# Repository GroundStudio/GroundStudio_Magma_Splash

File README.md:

GroundStudio Magma Splash
====================================

Get it from [ardushop.ro](https://ardushop.ro/ro/home/2496-placa-de-dezvoltare-magma-splash.html)

Explore all the GroundStudio products at [GroundStudio.ro](https://groundstudio.ro/)

Description
-------------------
STM32F411CEU6 based development board wih high-performance ARM® Cortex®-M4 32-bit RISC core operating at a frequency of up to 100 MHz, 512kBytes of Flash memory, 128kBytes SRAM, 24 PWM, 5 SPI, 3 UART, 32 Digital Pins and 10 channel 12 bit ADC Pins.

Contents
-------------------

* [/Documentation](https://github.com/GroundStudio/GroundStudio_Magma_Splash/tree/main/Documentation) -- Pinout.
* [/Hardware](https://github.com/GroundStudio/GroundStudio_Magma_Splash/tree/main/Hardware) -- Schematics, layout.

Versions
-------------------
*(Not all tags shown)*

* [REV0.01]

License
-------------------

This is released under the [Attribution-ShareAlike 4.0 International (CC BY-SA 4.0)](https://creativecommons.org/licenses/by-sa/4.0/) license.
**You are welcome to use this for commercial purposes.**

Please consider contributing back to this project or others to help the open-source hardware community continue to thrive and grow!

Certifications:

[Open Source Hardware Association](https://certification.oshwa.org/ro000009.html)   
   
[
](https://certification.oshwa.org/ro000009.html)

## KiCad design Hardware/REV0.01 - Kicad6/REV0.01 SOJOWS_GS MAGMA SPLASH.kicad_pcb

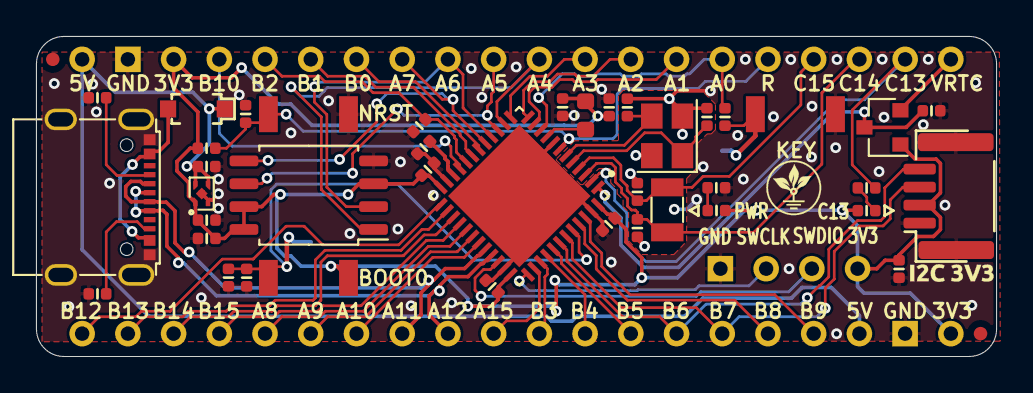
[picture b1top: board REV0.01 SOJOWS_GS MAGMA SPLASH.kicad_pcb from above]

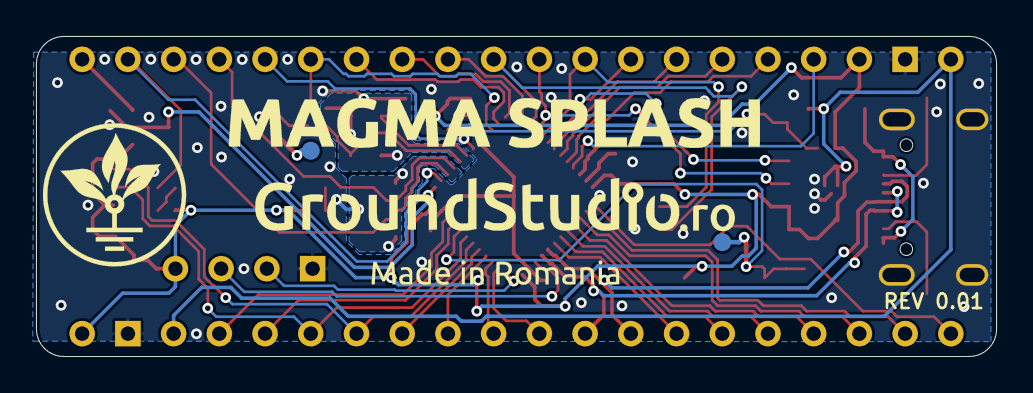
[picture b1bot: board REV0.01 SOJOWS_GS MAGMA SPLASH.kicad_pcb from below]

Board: 2 copper layers, 53.3 x 17.8 mm, 47 parts (2 on the bottom side), 51 nets.

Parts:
C1, C2, C3, C4, C5, C8, C9, C16, C17: 100nF; C_0402_1005Metric_Alternative
C6, C7, C10: 1uF; C_0402_1005Metric_Alternative
C11: 2.2uF; C_0402_1005Metric_Alternative
C12, C13, C14, C15: 12pF; C_0402_1005Metric_Alternative
D1: D_Schottky; SOD-123
D2: BAT54C; SOT-23
FID1, FID2: Fiducial; Fiducial_0.75mm_Mask1.5mm
J1, J2: Conn_01x20; PinHeader_1x20_P2.54mm_Vertical_Male
J3: Conn_01x04; PinHeader_1x04_P2.54mm_Vertical_Male
L1: L; L_0603_1608Metric
LED1: GREEN; LED_0402_1005Metric_Alternative
LED2: BLUE; LED_0402_1005Metric_Alternative
R1, R2, R4: 10k; R_0402_1005Metric_Alternative
R3: 330; R_0402_1005Metric_Alternative
R5, R6: 5.1k; R_0402_1005Metric_Alternative
R7, R8: 1k; R_0402_1005Metric_Alternative
RESET1: TS342A2P-WZ
SW1, SW2: TS342A2P-WZ
TP2: TestPoint
TPe: TestPoint
U1: ME6211C33U4AG-N; FBP1-1-4
U2: STM32F411CEU6; UFQFPN-48-1EP_7x7mm_P0.5mm_EP5.6x5.6mm
U3: W25Q32JVSSIQ; SOIC-8_5.275x5.275mm_P1.27mm
USB1: USB_C_FULL; USB_C_C167321
X1: i2c_3V3; SH__1x04_P1.00mm_Horizontal
Y1: SF32K32768D71T01; Crystal_SMD_3215-2Pin_3.2x1.5mm
Y2: S3225000121060; Crystal_SMD_3225-4Pin_3.2x2.5mm

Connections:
+3V3: C3.1, C4.1, C5.1, C7.1, C8.1, C9.1, C10.1, C16.1, D2.1, J1.3, J2.20, J3.4, L1.2, LED1.2, LED2.2, R1.1, SW2.2, U1.1, U2.24, U2.36, U2.48, U3.3, U3.7, U3.8, X1.2
+5V: C6.1, D1.1, J1.1, J2.18, U1.3, U1.4
A_D+: J2.9, U2.33, USB1.A6, USB1.B6
A_D-: J2.8, U2.32, USB1.A7, USB1.B7
BOOT0: C1.2, R2.1, SW2.1, TPe.~, U2.44
GND: C1.1, C2.2, C3.2, C4.2, C5.2, C6.2, C7.2, C8.2, C9.2, C10.2, C11.2, C12.2, C13.2, C14.2, C15.2, C16.2, C17.2, J1.2, J2.19, J3.1, R2.2, R4.2, R5.1, R6.2, R7.1, RESET1.1, SW1.2, U1.2, U1.5, U2.8, U2.23, U2.35, U2.47, U2.49, U3.4, USB1.0, USB1.A1, USB1.A12, USB1.B1, USB1.B12, X1.0, X1.1, Y2.2, Y2.4
NRST: C2.1, J1.16, R1.2, RESET1.2, U2.7
unnamed: C11.1, U2.22
unnamed: L1.1, U2.9
unnamed: LED1.1, R7.2
unnamed: LED2.1, R8.2
unnamed: R3.1, SW1.1, TP2.~
unnamed: R5.2, USB1.B5
unnamed: R6.1, USB1.A5
PA0: J1.15, R3.2, U2.10
PA1: J1.14, U2.11
PA2: J1.13, U2.12
PA3: J1.12, U2.13
PA4: J1.11, U2.14, U3.1
PA5: J1.10, U2.15, U3.6
PA6: J1.9, U2.16, U3.2
PA7: J1.8, U2.17, U3.5
PA8: J2.5, U2.29
PA9: J2.6, U2.30
PA10: J2.7, U2.31
PA15: J2.10, U2.38
PB0: J1.7, U2.18
PB1: J1.6, U2.19
PB2_BOOT1: J1.5, R4.1, U2.20
PB3: J2.11, U2.39
PB4: J2.12, U2.40
PB5: J2.13, U2.41
PB6: J2.14, U2.42, X1.4
PB7: J2.15, U2.43, X1.3
PB8: J2.16, U2.45
PB9: J2.17, U2.46
PB10: J1.4, U2.21
PB12: J2.1, U2.25
PB13: J2.2, U2.26
PB14: J2.3, U2.27
PB15: J2.4, U2.28
PC13: J1.19, R8.1, U2.2
PC14_OSC32_IN: C12.1, J1.18, U2.3, Y1.2
PC15_OSC32_OUT: C13.1, J1.17, U2.4, Y1.1
PH0-OSC_IN: C14.1, U2.5, Y2.1
PH1-OSC_OUT: C15.1, U2.6, Y2.3
SWCLK: J3.2, U2.37
SWDIO: J3.3, U2.34
VBAT: C17.1, D2.3, U2.1
VBUS: D1.2, USB1.A4, USB1.A9, USB1.B4, USB1.B9
VRTC: D2.2, J1.20

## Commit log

2022-08-09 - initial commit
2022-08-26 - added schematic pdf file
2022-08-26 - added "Kicad6" to revision folder name
2023-03-15 Update README.md
    - removed references to "library"
2023-11-03 - added datasheet
